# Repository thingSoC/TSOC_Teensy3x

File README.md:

# TSOC_Teensy3x

The **TSOC_Teensy3x** is an adapter board for the excellent [Teensy Development Board](https://www.pjrc.com/teensy/) from [PJRC](https://www.pjrc.com/).

The **TSOC_Teensy3x** allows you to connect [thingSoC](http://thingsoc.github.io/), [Mikrobus](http://www.mikroe.com/mikrobus/), 
and/or [Grove System](http://www.seeedstudio.com/blog/2016/03/09/tutorial-intro-to-grove-connectors-for-arduinoraspberry-pi-projects/) 
Modules all at the same time, either standalone, or with any other thingSoC Processor or Radio module.
This gives you maximum flexiblity for sensor and actuator selection and reuse. 

[TSOC_TEENSY3X](https://github.com/thingSoC/TSOC_TEENSY3X)

The thingSoC "Grovey Series" was designed as "Everyday Electronics", a no-frills, low cost, approach to modular embedded product design.
thingSoC boards are similar in size to most break-out-boards (BOBs), but feature a standardized stacking pinout, as well as an I2C metadata store (EEPROM)
to indicate what peripherals are installed.

---------------------------------------

## TSOC_TEENSY3X Application Pictures

In this example, we use the [Grovey_I2CHUB](https://github.com/thingSoC/TSOC_GROVEY_I2CHUB) with the [Teensy3.x Adapter](https://github.com/thingSoC/TSOC_Teensy3x)
to support a Grove 16x2 LCD panel.

Since the Grove 16x2 LCD panel is a 5V peripheral, the [Grovey_I2CHUB](https://github.com/thingSoC/TSOC_GROVEY_I2CHUB) performs the voltage level translation
necessary to go from the 3.3V Teensy3.x processor to the 5V LCD controller. The [Teensy3.x Adapter](https://github.com/thingSoC/TSOC_Teensy3x) also has an I2C output jack, but it is at a 3.3V level,
and so, the [Grovey_I2CHUB](https://github.com/thingSoC/TSOC_GROVEY_I2CHUB) is necessary to convert to 5V I2C outputs.

[*TSOC_TEENSY3X*](https://github.com/thingSoC/TSOC_TEENSY3X)

---------------------------------------

## TSOC_Teensy3x with Mikrobus "Click" peripherals

The [Teensy3.x Adapter](https://github.com/thingSoC/TSOC_Teensy3x) also allows you to plug in [Mikrobus](http://www.mikroe.com/mikrobus/) 
peripherals and ["Click Modules"](http://www.mikroe.com/click/), and use these along with the 
[Grove System](http://www.seeedstudio.com/blog/2016/03/09/tutorial-intro-to-grove-connectors-for-arduinoraspberry-pi-projects/) modules. 

[*TSOC_TEENSY3X*](https://github.com/thingSoC/TSOC_TEENSY3X)

---------------------------------------

## TSOC_TEENSY3X Arduino Sketch Examples

Under the Arduino "examples" directory are many Arduino IDE examples for using the Teensy board with Arduino IDE,
provided by [PJRC](https://www.pjrc.com/). Paul provides [setup and installation instructions](https://www.pjrc.com/teensy/tutorial.html) for the Teensy.
What the **TSOC_Teensy3x** adaptor board provides is an easy "plug-n-play" way to connect many different peripherals to the Teensy.

---------------------------------------

## TSOC_TEENSY3X Status <a name="TSOC_TEENSY3X_status"/>

**09/02/2016:** 
Revision 1.0 - Initial Layout - SPI PINS D11/D12 reversed!
Revision 2.0 - Fix SPI Pins, add Analog I/O

---------------------------------------
## TSOC_TEENSY3X Images

[TSOC_TEENSY3X](https://github.com/thingSoC/TSOC_TEENSY3X)

---------------------------------------

## TSOC_TEENSY3X Documentation Index <a name="TSOC_TEENSY3X_documentation_index"/>

[TSOC_TEENSY3X Project](https://github.com/thingSoC/TSOC_Teensy3x)

[TSOC_TEENSY3X Hardware](https://github.com/thingSoC/TSOC_Teensy3x/tree/master/TSOC_Teensy3x/hardware)

---------------------------------------

## thingSoC Documentation Index <a name="thingSoC_documentation_index"/>

[thingSoC Organization Website](http://thingSoC.github.io)

[thingSoC FAQ - Frequently Asked Questions](http://thingsoc.github.io/support/faq.html)

---------------------------------------

[ 
*thingSoC*](http://thingsoc.github.io)

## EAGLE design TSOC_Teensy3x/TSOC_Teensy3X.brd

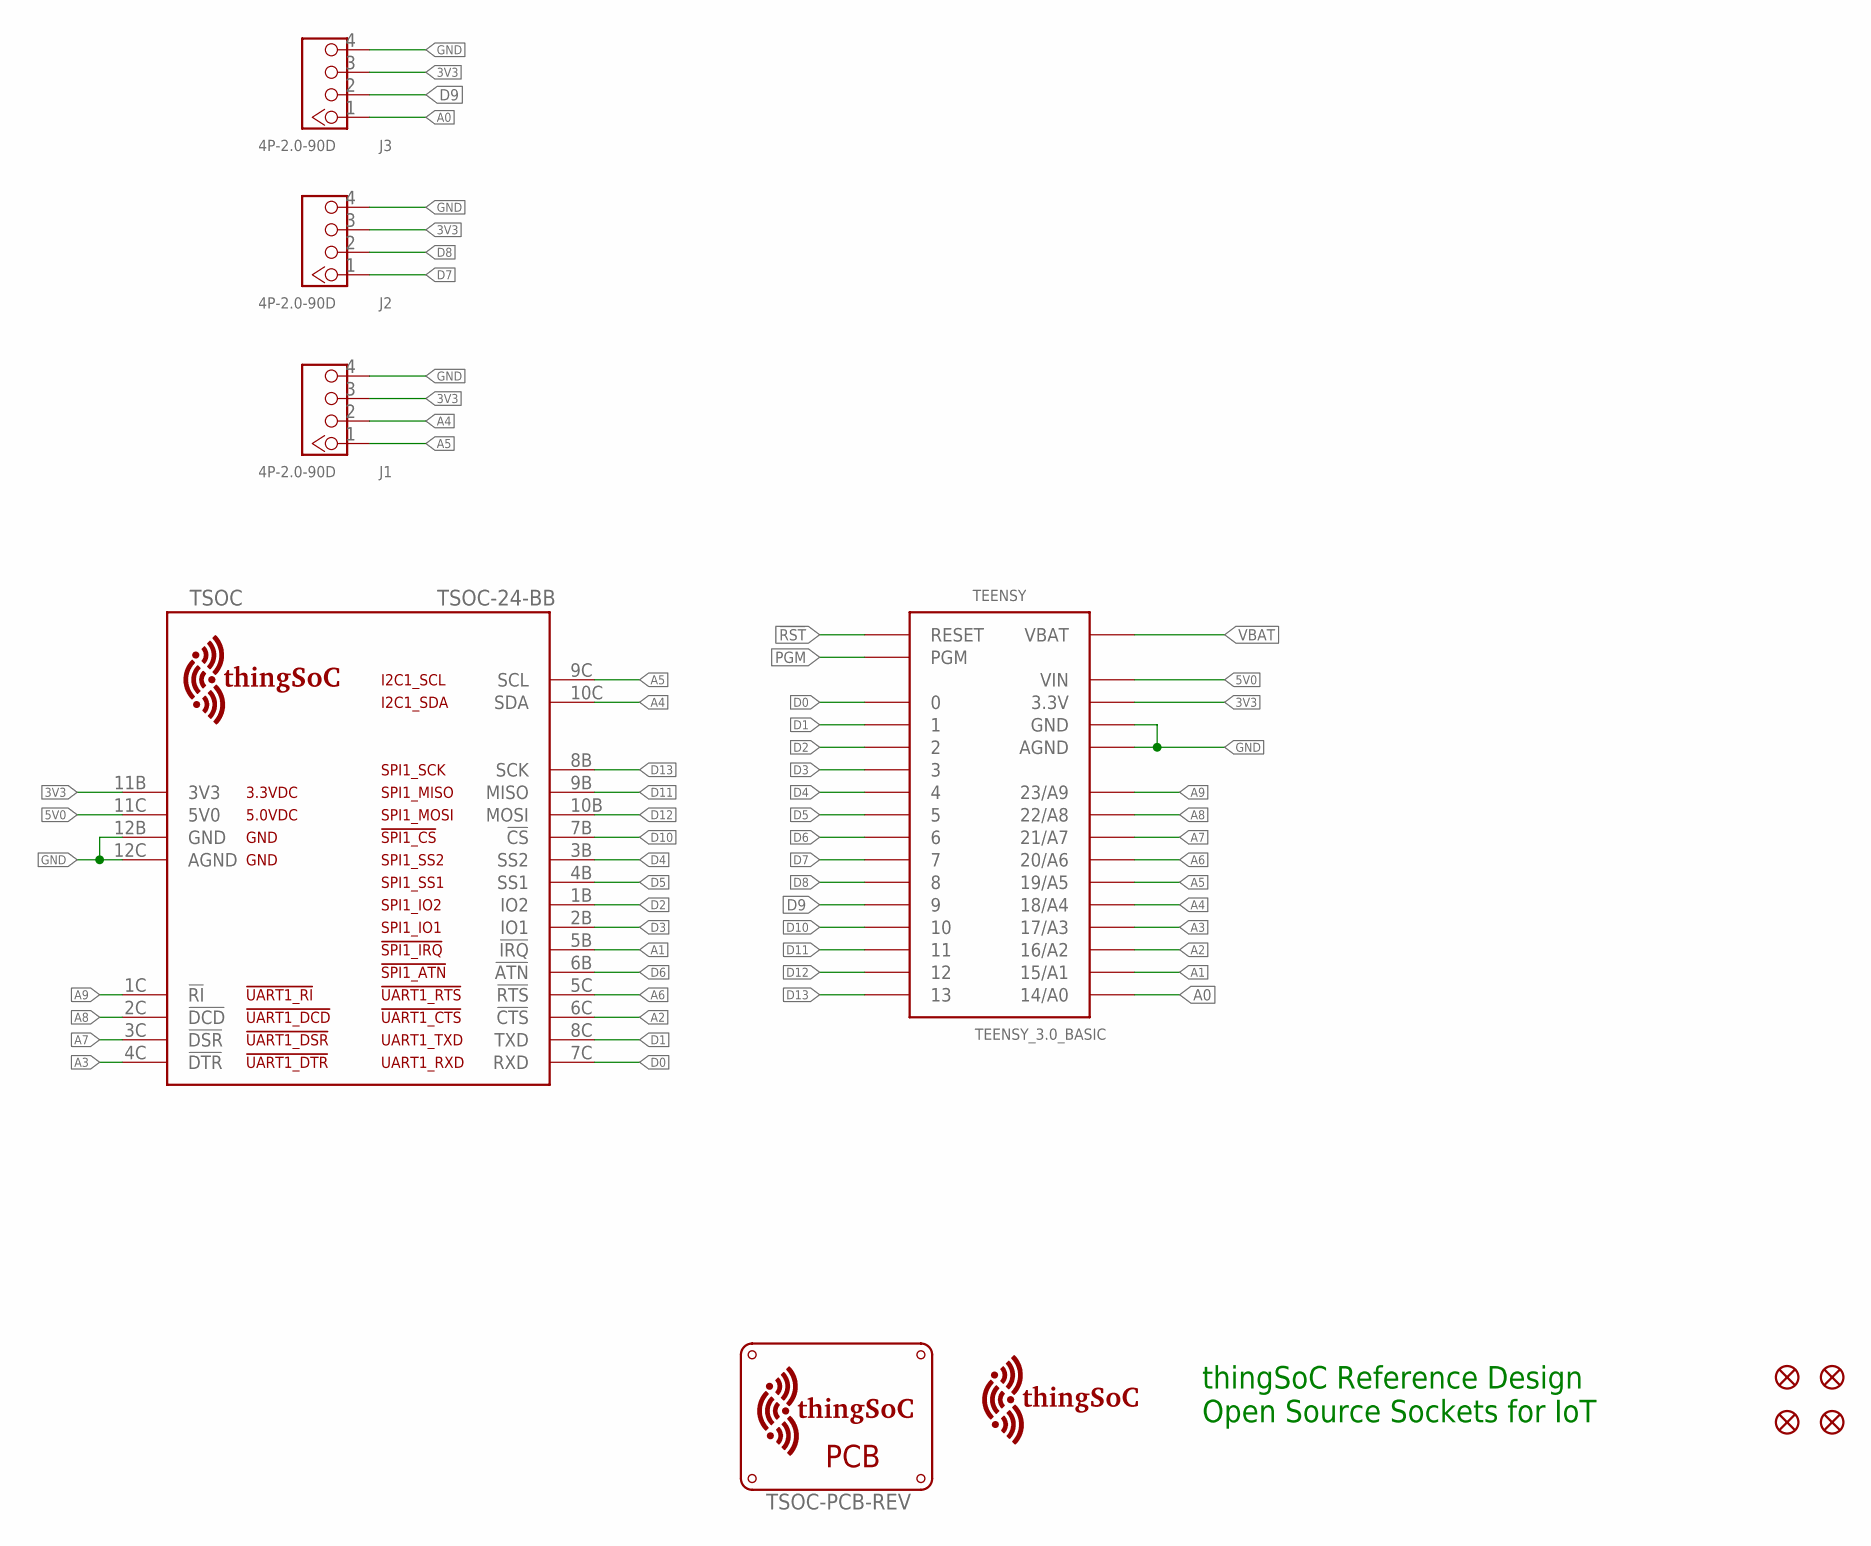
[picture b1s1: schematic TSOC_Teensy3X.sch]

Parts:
FID1, FID2, FID3, FID4: FIDUCIALUFIDUCIAL; MICRO-FIDUCIAL
J1, J2, J3: 4P-2.0-90D; HW4-2.0-90D
TEENSY: TEENSY_3.0_BASIC
TSOC: TSOC-24-BB; TSOC-BB-S24
U$2: TSOC-PCB-REV; TSOC-BB-BRD-PLUS-CUT-REV
U$5: TSOC-LOGO-LRG

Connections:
3V3: J1.3, J2.3, J3.3, TEENSY.3.3V, TEENSY.3.3V1 (3.3V), TSOC.11B (3V3)
5V0: TEENSY.VIN, TSOC.11C (5V0)
!RST: TEENSY.RESET
A0: J3.1, TEENSY.14/A0
A1: TEENSY.15/A1, TSOC.5B (!IRQ)
A2: TEENSY.16/A2, TSOC.6C (!CTS)
A3: TEENSY.17/A3, TSOC.4C (!DTR)
A4: J1.2, TEENSY.18/A4, TSOC.10C (SDA)
A5: J1.1, TEENSY.19/A5, TSOC.9C (SCL)
A6: TEENSY.20/A6, TSOC.5C (!RTS)
A7: TEENSY.21/A7, TSOC.3C (!DSR)
A8: TEENSY.22/A8, TSOC.2C (!DCD)
A9: TEENSY.23/A9, TSOC.1C (!RI)
D0: TEENSY.0, TSOC.7C (RXD)
D1: TEENSY.1, TSOC.8C (TXD)
D2: TEENSY.2, TSOC.1B (IO2)
D3: TEENSY.3, TSOC.2B (IO1)
D4: TEENSY.4, TSOC.3B (SS2)
D5: TEENSY.5, TSOC.4B (SS1)
D6: TEENSY.6, TSOC.6B (!ATN)
D7: J2.1, TEENSY.7
D8: J2.2, TEENSY.8
D9: J3.2, TEENSY.9
D10: TEENSY.10, TSOC.7B (!CS)
D11: TEENSY.11, TSOC.9B (MISO)
D12: TEENSY.12, TSOC.10B (MOSI)
D13: TEENSY.13, TSOC.8B (SCK)
GND: J1.4, J2.4, J3.4, TEENSY.AGND, TEENSY.GND, TEENSY.GND1 (GND), TSOC.12B (GND), TSOC.12C (AGND)
PGM: TEENSY.PGM
VBAT: TEENSY.VBAT

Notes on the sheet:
thingSoC Reference Design Open Source Sockets for IoT

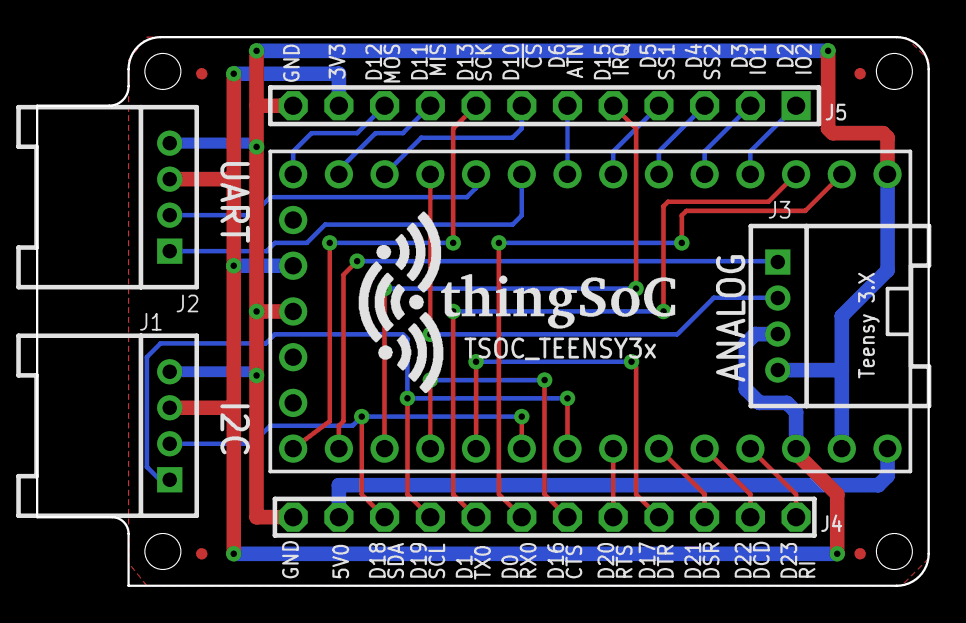
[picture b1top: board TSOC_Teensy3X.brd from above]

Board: 2 copper layers, 49.5 x 30.5 mm, 12 parts (1 on the bottom side), 27 nets.

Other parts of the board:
U$1: TSOC-LOGO-LRG

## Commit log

2016-09-03 initial version
2016-09-03 add product images
2016-09-04 update docs
2016-10-17 update BOM
2017-01-10 update documentation
2017-01-16 update documetation

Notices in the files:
parts and their libraries:
thingSoC: License : http://creativecommons.org/licenses/by-sa/4.0
(Creative Commons 4.0)
PatternAgents-Beautify: License : http://creativecommons.org/licenses/by-sa/3.0
(Creative Commons 3.0)
